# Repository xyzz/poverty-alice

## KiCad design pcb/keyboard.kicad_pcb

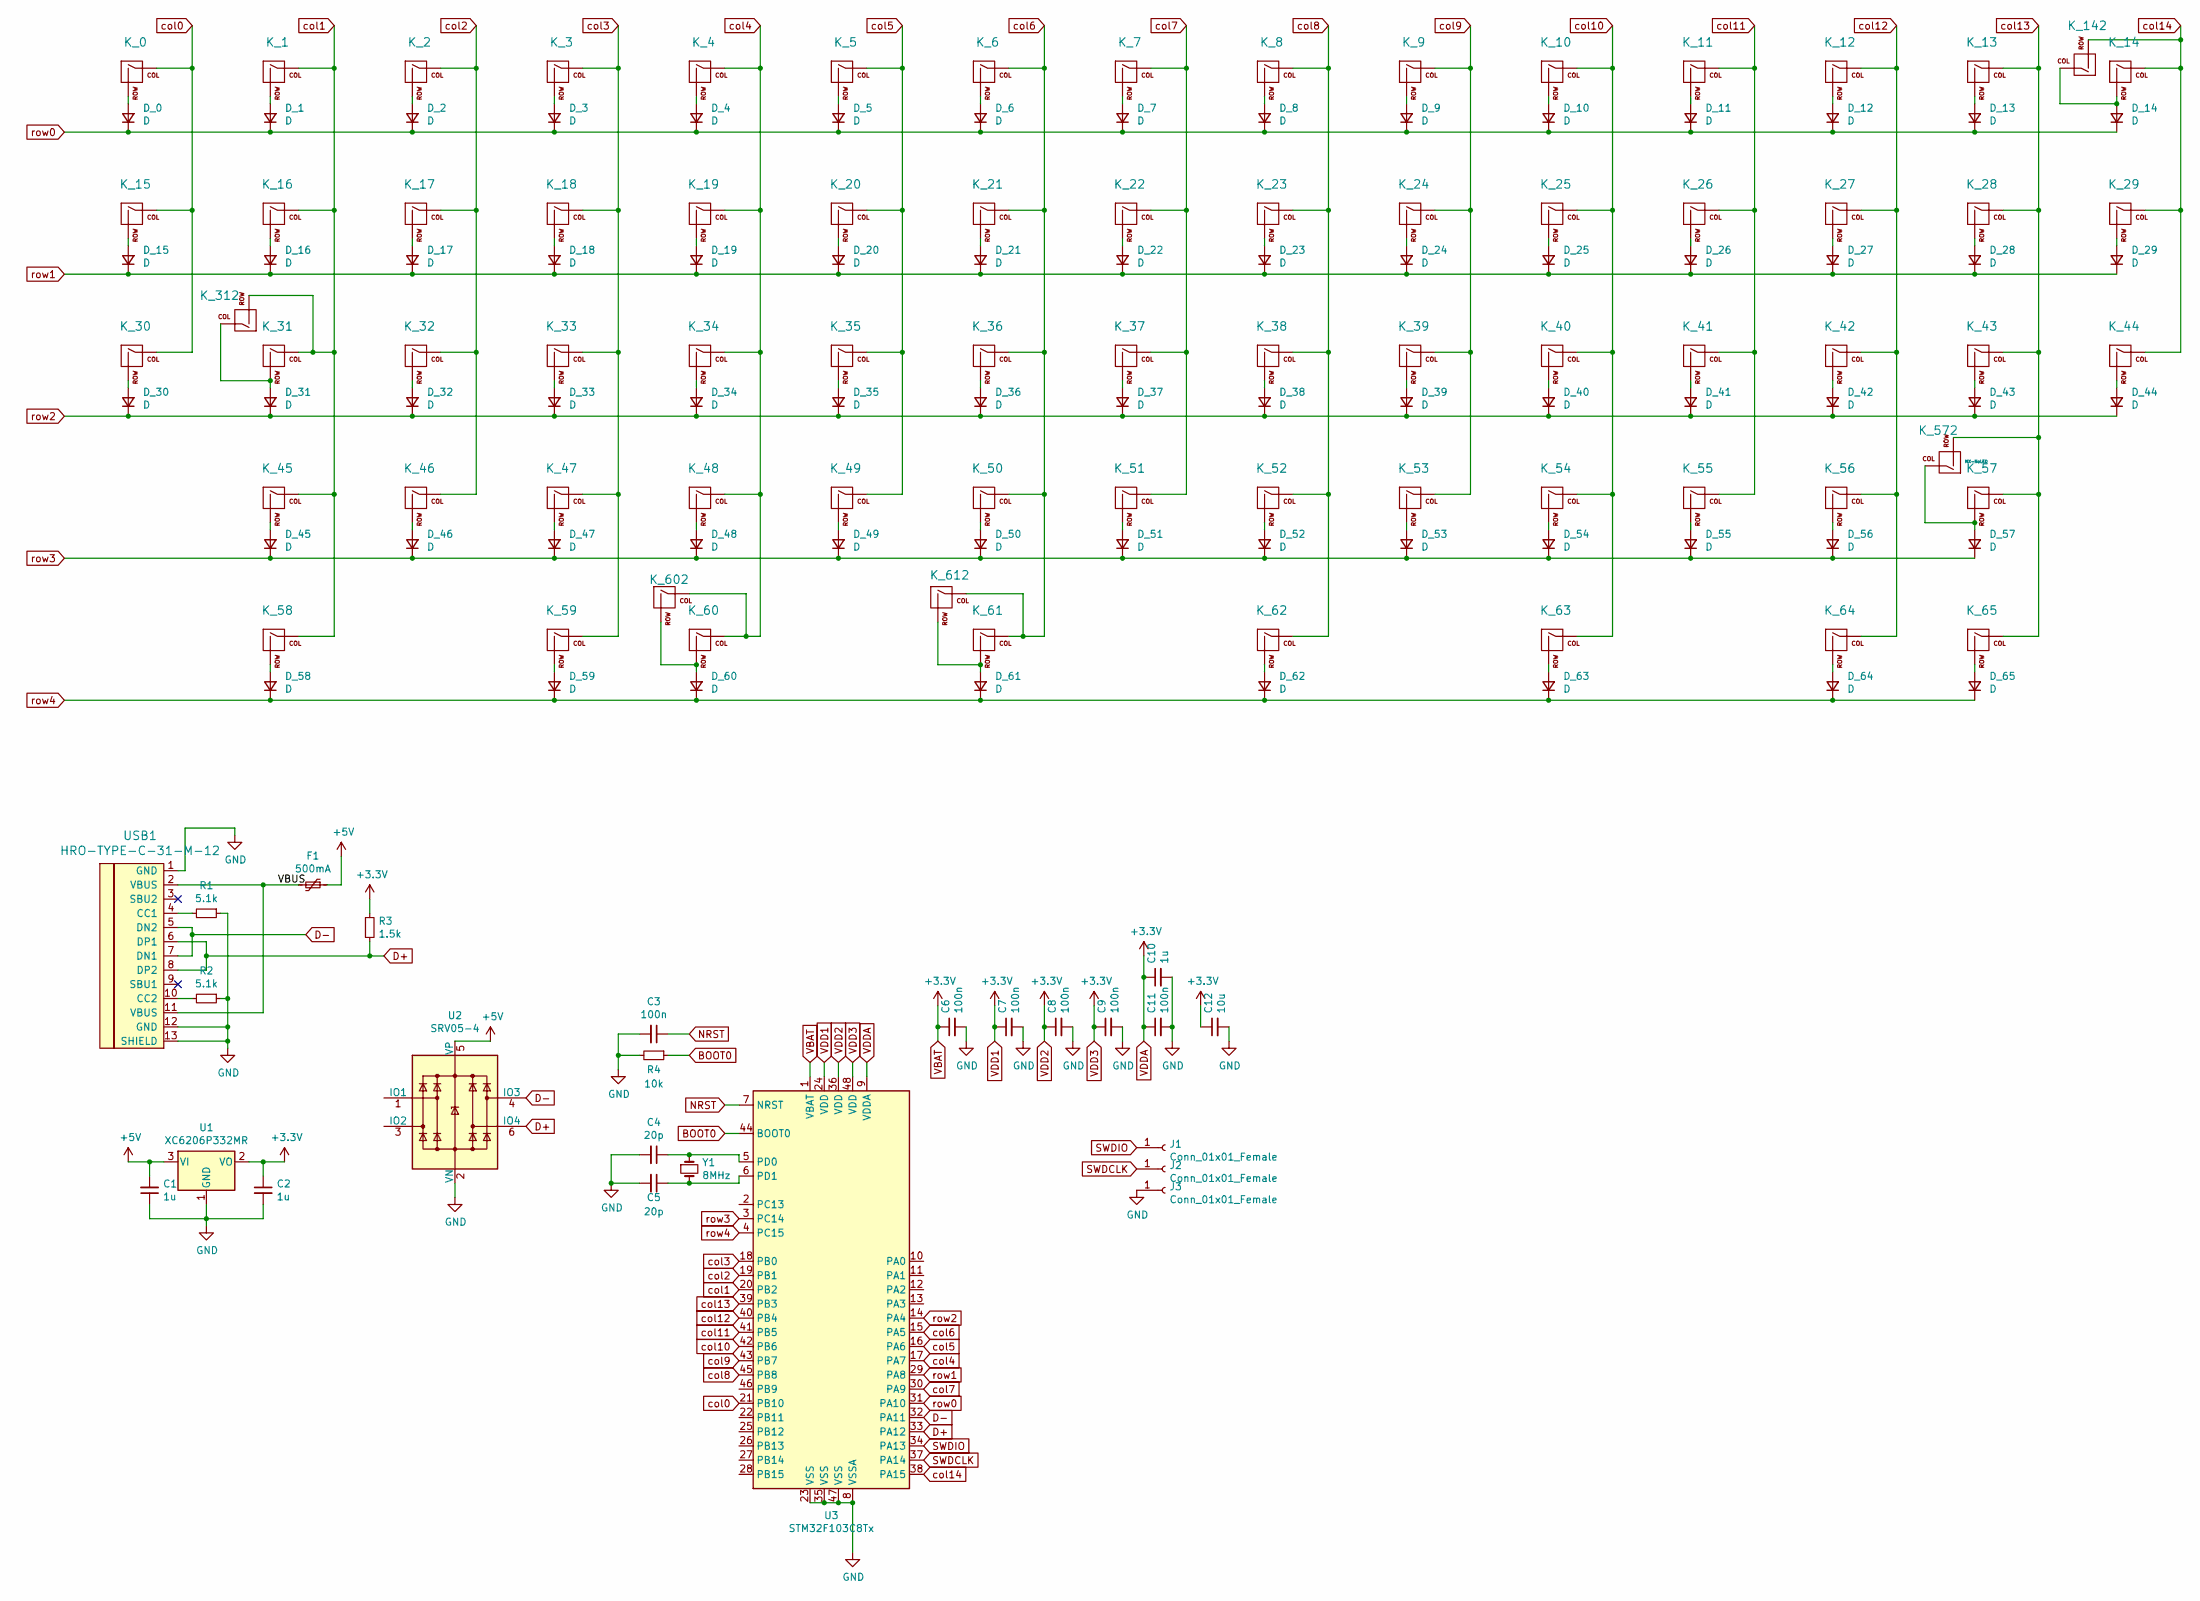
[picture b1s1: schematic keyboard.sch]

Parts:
C1, C2, C10: 1u; C_0603_1608Metric; JLC C15849
C3, C6, C7, C8, C9, C11: 100n; C_0603_1608Metric; JLC C14663
C4, C5: 20p; C_0603_1608Metric; JLC C1648
C12: 10u; C_0603_1608Metric; JLC C19702
D_0, D_1, D_2, D_3, D_4, D_5, D_6, D_7, D_8, D_9, D_10, D_11, D_12, D_13, D_14, D_15, D_16, D_17, D_18, D_19, D_20, D_21, D_22, D_23, D_24, D_25, D_26, D_27, D_28, D_29, D_30, D_31, D_32, D_33, D_34, D_35, D_36, D_37, D_38, D_39, D_40, D_41, D_42, D_43, D_44, D_45, D_46, D_47, D_48, D_49, D_50, D_51, D_52, D_53, D_54, D_55, D_56, D_57, D_58, D_59, D_60, D_61, D_62, D_63, D_64, D_65: D; D_SOD-123; JLC C64898
F1: 500mA; Fuse_1206_3216Metric; JLC C369159
J1, J2, J3: Conn_01x01_Female; TestPoint_Pad_D1.5mm
K_0, K_1, K_2, K_3, K_4, K_5, K_6, K_7, K_8, K_9, K_10, K_11, K_12, K_13, K_14, K_15, K_17, K_18, K_19, K_20, K_21, K_22, K_23, K_24, K_25, K_26, K_27, K_28, K_29, K_30, K_32, K_33, K_34, K_35, K_36, K_37, K_38, K_39, K_40, K_41, K_42, K_46, K_47, K_48, K_49, K_50, K_51, K_52, K_53, K_54, K_55, K_56, K_65: KEYSW; MXOnly-1U-NoLED
K_16, K_44, K_58, K_59, K_63, K_64: KEYSW; MXOnly-1.5U-NoLED
K_31, K_57: KEYSW; MXOnly-1.75U-NoLED
K_43: KEYSW; MXOnly-2.25U-ReversedStabilizers-NoLED
K_45: KEYSW; MXOnly-2.25U-NoLED
K_60: KEYSW; MXOnly-2U-ReversedStabilizers-NoLED
K_61: KEYSW; MXOnly-1.25U-NoLED
K_62: KEYSW; MXOnly-2.75U-ReversedStabilizers-NoLED
K_142: MX-NoLED; MXOnly-2U-NoLED
K_312, K_612: MX-NoLED; MXOnly-1U-NoLED
K_572: MX-NoLED; MXOnly-2.75U-NoLED
K_602: MX-NoLED; MXOnly-2.25U-ReversedStabilizers-NoLED
R1, R2: 5.1k; R_0603_1608Metric; JLC C23186
R3: 1.5k; R_0603_1608Metric; JLC C22843
R4: 10k; R_0603_1608Metric; JLC C25804
U1: XC6206P332MR; SOT-23; JLC C5446
U2: SRV05-4; SOT-23-6; JLC C85364
U3: STM32F103C8Tx; LQFP-48_7x7mm_P0.5mm; JLC C8734
USB1: HRO-TYPE-C-31-M-12; HRO-TYPE-C-31-M-12-jlc
Y1: 8MHz; Crystal_SMD_5032-2Pin_5.0x3.2mm; JLC C115962

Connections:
+5V: C1.2, F1.1, U1.3 (VI), U2.5 (VP)
/VBUS: F1.2, USB1.2 (VBUS), USB1.11 (VBUS)
BOOT0: R4.1, U3.44 (BOOT0)
D+: R3.2, U2.6 (IO4), U3.33 (PA12), USB1.6 (DP1), USB1.8 (DP2)
D-: U2.4 (IO3), U3.32 (PA11), USB1.5 (DN2), USB1.7 (DN1)
GND: C1.1, C2.2, C3.2, C4.2, C5.2, C6.2, C7.2, C8.2, C9.2, C10.2, C11.2, C12.2, J3.1, R1.1, R2.1, R4.2, U1.1 (GND), U2.2 (VN), U3.8 (VSSA), U3.23 (VSS), U3.35 (VSS), U3.47 (VSS), USB1.1 (GND), USB1.12 (GND), USB1.13 (SHIELD)
NRST: C3.1, U3.7 (NRST)
unnamed: C4.1, U3.5 (PD0), Y1.1
unnamed: C5.1, U3.6 (PD1), Y1.2
unnamed: D_0.2 (A), K_0.2 (ROW)
unnamed: D_1.2 (A), K_1.2 (ROW)
unnamed: D_2.2 (A), K_2.2 (ROW)
unnamed: D_3.2 (A), K_3.2 (ROW)
unnamed: D_4.2 (A), K_4.2 (ROW)
unnamed: D_5.2 (A), K_5.2 (ROW)
unnamed: D_6.2 (A), K_6.2 (ROW)
unnamed: D_7.2 (A), K_7.2 (ROW)
unnamed: D_8.2 (A), K_8.2 (ROW)
unnamed: D_9.2 (A), K_9.2 (ROW)
unnamed: D_10.2 (A), K_10.2 (ROW)
unnamed: D_11.2 (A), K_11.2 (ROW)
unnamed: D_12.2 (A), K_12.2 (ROW)
unnamed: D_13.2 (A), K_13.2 (ROW)
unnamed: D_14.2 (A), K_14.2 (ROW), K_142.1 (COL)
unnamed: D_15.2 (A), K_15.2 (ROW)
unnamed: D_16.2 (A), K_16.2 (ROW)
unnamed: D_17.2 (A), K_17.2 (ROW)
unnamed: D_18.2 (A), K_18.2 (ROW)
unnamed: D_19.2 (A), K_19.2 (ROW)
unnamed: D_20.2 (A), K_20.2 (ROW)
unnamed: D_21.2 (A), K_21.2 (ROW)
unnamed: D_22.2 (A), K_22.2 (ROW)
unnamed: D_23.2 (A), K_23.2 (ROW)
unnamed: D_24.2 (A), K_24.2 (ROW)
unnamed: D_25.2 (A), K_25.2 (ROW)
unnamed: D_26.2 (A), K_26.2 (ROW)
unnamed: D_27.2 (A), K_27.2 (ROW)
unnamed: D_28.2 (A), K_28.2 (ROW)
unnamed: D_29.2 (A), K_29.2 (ROW)
unnamed: D_30.2 (A), K_30.2 (ROW)
unnamed: D_31.2 (A), K_31.2 (ROW), K_312.1 (COL)
unnamed: D_32.2 (A), K_32.2 (ROW)
unnamed: D_33.2 (A), K_33.2 (ROW)
unnamed: D_34.2 (A), K_34.2 (ROW)
unnamed: D_35.2 (A), K_35.2 (ROW)
unnamed: D_36.2 (A), K_36.2 (ROW)
unnamed: D_37.2 (A), K_37.2 (ROW)
unnamed: D_38.2 (A), K_38.2 (ROW)
unnamed: D_39.2 (A), K_39.2 (ROW)
unnamed: D_40.2 (A), K_40.2 (ROW)
unnamed: D_41.2 (A), K_41.2 (ROW)
unnamed: D_42.2 (A), K_42.2 (ROW)
unnamed: D_43.2 (A), K_43.2 (ROW)
unnamed: D_44.2 (A), K_44.2 (ROW)
unnamed: D_45.2 (A), K_45.2 (ROW)
unnamed: D_46.2 (A), K_46.2 (ROW)
unnamed: D_47.2 (A), K_47.2 (ROW)
unnamed: D_48.2 (A), K_48.2 (ROW)
unnamed: D_49.2 (A), K_49.2 (ROW)
unnamed: D_50.2 (A), K_50.2 (ROW)
unnamed: D_51.2 (A), K_51.2 (ROW)
unnamed: D_52.2 (A), K_52.2 (ROW)
unnamed: D_53.2 (A), K_53.2 (ROW)
unnamed: D_54.2 (A), K_54.2 (ROW)
unnamed: D_55.2 (A), K_55.2 (ROW)
unnamed: D_56.2 (A), K_56.2 (ROW)
unnamed: D_57.2 (A), K_57.2 (ROW), K_572.1 (COL)
unnamed: D_58.2 (A), K_58.2 (ROW)
unnamed: D_59.2 (A), K_59.2 (ROW)
unnamed: D_60.2 (A), K_60.2 (ROW), K_602.2 (ROW)
unnamed: D_61.2 (A), K_61.2 (ROW), K_612.2 (ROW)
unnamed: D_62.2 (A), K_62.2 (ROW)
unnamed: D_63.2 (A), K_63.2 (ROW)
unnamed: D_64.2 (A), K_64.2 (ROW)
unnamed: D_65.2 (A), K_65.2 (ROW)
unnamed: R1.2, USB1.4 (CC1)
unnamed: R2.2, USB1.10 (CC2)
SWDCLK: J2.1, U3.37 (PA14)
SWDIO: J1.1, U3.34 (PA13)
VBAT: C2.1, C6.1, C7.1, C8.1, C9.1, C10.1, C11.1, C12.1, R3.1, U1.2 (VO), U3.1 (VBAT), U3.9 (VDDA), U3.24 (VDD), U3.36 (VDD), U3.48 (VDD)
col0: K_0.1 (COL), K_15.1 (COL), K_30.1 (COL), U3.21 (PB10)
col1: K_1.1 (COL), K_16.1 (COL), K_31.1 (COL), K_45.1 (COL), K_58.1 (COL), K_312.2 (ROW), U3.20 (PB2)
col2: K_2.1 (COL), K_17.1 (COL), K_32.1 (COL), K_46.1 (COL), U3.19 (PB1)
col3: K_3.1 (COL), K_18.1 (COL), K_33.1 (COL), K_47.1 (COL), K_59.1 (COL), U3.18 (PB0)
col4: K_4.1 (COL), K_19.1 (COL), K_34.1 (COL), K_48.1 (COL), K_60.1 (COL), K_602.1 (COL), U3.17 (PA7)
col5: K_5.1 (COL), K_20.1 (COL), K_35.1 (COL), K_49.1 (COL), U3.16 (PA6)
col6: K_6.1 (COL), K_21.1 (COL), K_36.1 (COL), K_50.1 (COL), K_61.1 (COL), K_612.1 (COL), U3.15 (PA5)
col7: K_7.1 (COL), K_22.1 (COL), K_37.1 (COL), K_51.1 (COL), U3.30 (PA9)
col8: K_8.1 (COL), K_23.1 (COL), K_38.1 (COL), K_52.1 (COL), K_62.1 (COL), U3.45 (PB8)
col9: K_9.1 (COL), K_24.1 (COL), K_39.1 (COL), K_53.1 (COL), U3.43 (PB7)
col10: K_10.1 (COL), K_25.1 (COL), K_40.1 (COL), K_54.1 (COL), K_63.1 (COL), U3.42 (PB6)
col11: K_11.1 (COL), K_26.1 (COL), K_41.1 (COL), K_55.1 (COL), U3.41 (PB5)
col12: K_12.1 (COL), K_27.1 (COL), K_42.1 (COL), K_56.1 (COL), K_64.1 (COL), U3.40 (PB4)
col13: K_13.1 (COL), K_28.1 (COL), K_43.1 (COL), K_57.1 (COL), K_65.1 (COL), K_572.2 (ROW), U3.39 (PB3)
col14: K_14.1 (COL), K_29.1 (COL), K_44.1 (COL), K_142.2 (ROW), U3.38 (PA15)
row0: D_0.1 (K), D_1.1 (K), D_2.1 (K), D_3.1 (K), D_4.1 (K), D_5.1 (K), D_6.1 (K), D_7.1 (K), D_8.1 (K), D_9.1 (K), D_10.1 (K), D_11.1 (K), D_12.1 (K), D_13.1 (K), D_14.1 (K), U3.31 (PA10)
row1: D_15.1 (K), D_16.1 (K), D_17.1 (K), D_18.1 (K), D_19.1 (K), D_20.1 (K), D_21.1 (K), D_22.1 (K), D_23.1 (K), D_24.1 (K), D_25.1 (K), D_26.1 (K), D_27.1 (K), D_28.1 (K), D_29.1 (K), U3.29 (PA8)
row2: D_30.1 (K), D_31.1 (K), D_32.1 (K), D_33.1 (K), D_34.1 (K), D_35.1 (K), D_36.1 (K), D_37.1 (K), D_38.1 (K), D_39.1 (K), D_40.1 (K), D_41.1 (K), D_42.1 (K), D_43.1 (K), D_44.1 (K), U3.14 (PA4)
row3: D_45.1 (K), D_46.1 (K), D_47.1 (K), D_48.1 (K), D_49.1 (K), D_50.1 (K), D_51.1 (K), D_52.1 (K), D_53.1 (K), D_54.1 (K), D_55.1 (K), D_56.1 (K), D_57.1 (K), U3.3 (PC14)
row4: D_58.1 (K), D_59.1 (K), D_60.1 (K), D_61.1 (K), D_62.1 (K), D_63.1 (K), D_64.1 (K), D_65.1 (K), U3.4 (PC15)

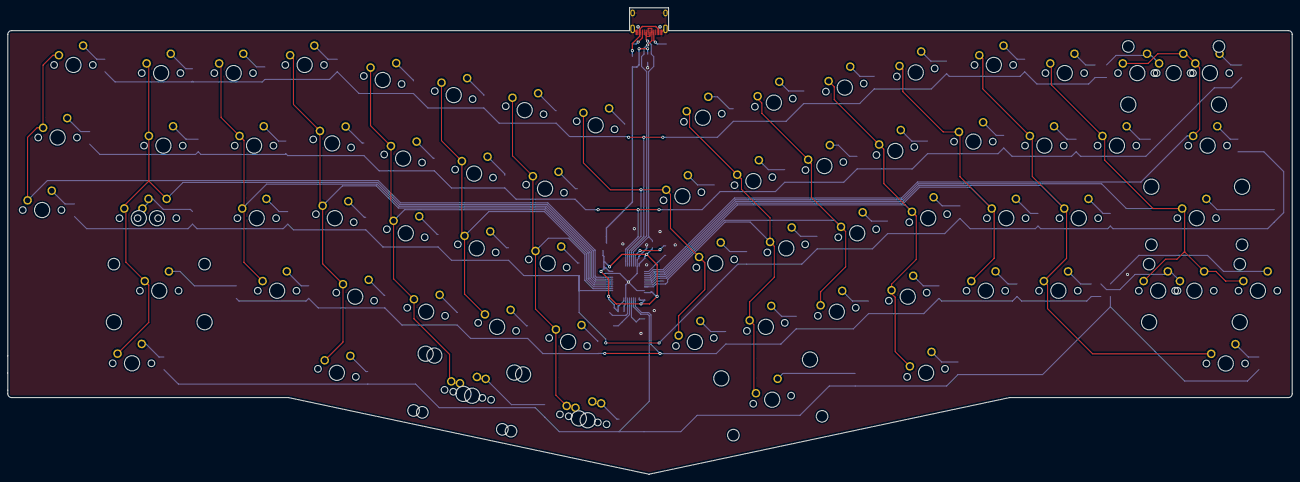
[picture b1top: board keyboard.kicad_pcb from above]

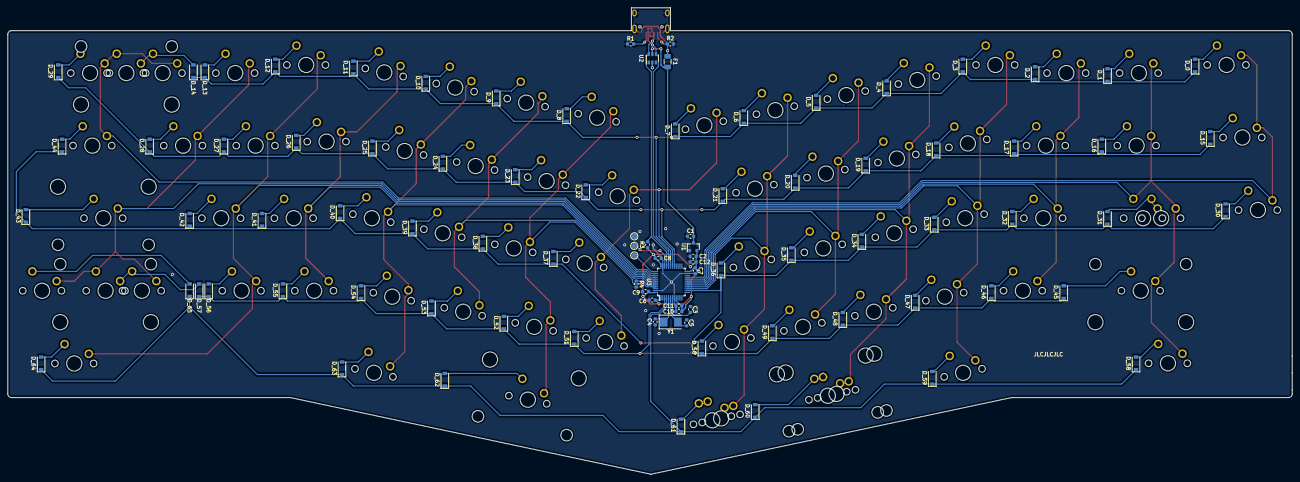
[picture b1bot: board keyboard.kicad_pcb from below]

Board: 2 copper layers, 337.2 x 122.5 mm, 162 parts (90 on the bottom side), 100 nets.

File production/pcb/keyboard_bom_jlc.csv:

"Comment","Designator","Footprint","LCSC Part #"
"20p","C4,C5","C_0603_1608Metric","C1648"
"100n","C6,C7,C8,C9,C11,C3","C_0603_1608Metric","C14663"
"1u","C10,C2,C1","C_0603_1608Metric","C15849"
"10u","C12","C_0603_1608Metric","C19702"
"D","D_0,D_1,D_2,D_3,D_4,D_5,D_6,D_7,D_8,D_9,D_10,D_11,D_12,D_13,D_14,D_15,D_16,D_17,D_18,D_19,D_20,D_21,D_22,D_23,D_24,D_25,D_26,D_27,D_28,D_29,D_30,D_31,D_32,D_33,D_34,D_35,D_36,D_37,D_38,D_39,D_40,D_41,D_42,D_43,D_44,D_45,D_46,D_47,D_48,D_49,D_50,D_51,D_52,D_53,D_54,D_55,D_56,D_57,D_58,D_59,D_60,D_61,D_62,D_63,D_64,D_65","D_SOD-123","C64898"
"500mA","F1","Fuse_1206_3216Metric","C369159"
"5.1k","R1,R2","R_0603_1608Metric","C23186"
"1.5k","R3","R_0603_1608Metric","C22843"
"10k","R4","R_0603_1608Metric","C25804"
"XC6206P332MR","U1","SOT-23","C5446"
"SRV05-4","U2","SOT-23-6","C85364"
"STM32F103C8Tx","U3","LQFP-48_7x7mm_P0.5mm","C8734"
"8MHz","Y1","Crystal_SMD_5032-2Pin_5.0x3.2mm","C115962"

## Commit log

2020-06-27 initial
